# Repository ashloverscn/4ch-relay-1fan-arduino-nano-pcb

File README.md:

# 4ch-relay-1fan-arduino-nano-pcb
4ch-relay-1fan-arduino-nano-pcb

firmware written in arduino : 

https://github.com/ashloverscn/ArduinoNano-4ch_Relay_and_1_Fan

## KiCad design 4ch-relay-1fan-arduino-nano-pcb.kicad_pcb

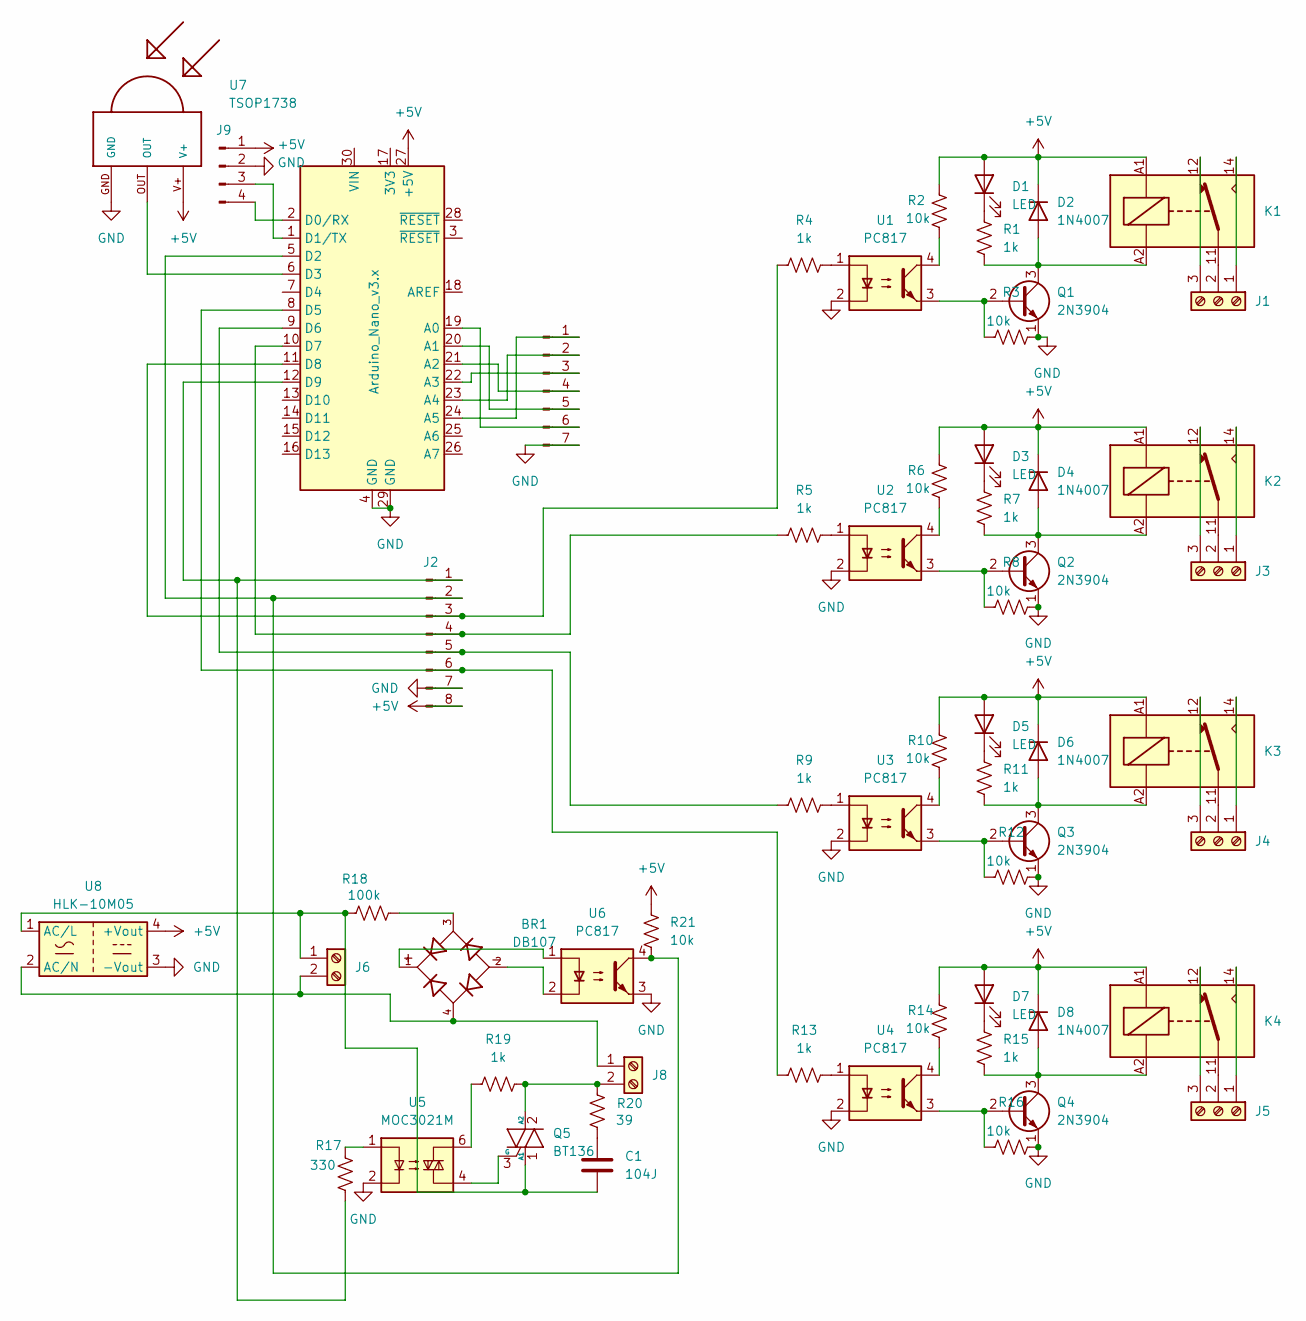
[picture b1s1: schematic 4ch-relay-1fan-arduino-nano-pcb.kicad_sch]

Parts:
A1: Arduino_Nano_v3.x; Arduino_Nano
BR1: DB107; DIP825W50P509L880H320Q4; PARTREV 13
C1: 104J; C_Disc_D16.0mm_W5.0mm_P10.00mm
D1, D3, D5, D7: LED; LED_D5.0mm
D2, D4, D6, D8: 1N4007; D_DO-41_SOD81_P10.16mm_Horizontal
J1, J3, J4, J5: Screw_Terminal_01x03; TerminalBlock_Phoenix_MKDS-1,5-3-5.08_1x03_P5.08mm_Horizont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
J2: Conn_01x08_Pin; PinHeader_1x08_P2.54mm_Vertical
J6, J8: TerminalBlock_MaiXu_MX126-5.0-02P_1x02_P5.00mm
J7: Conn_01x07_Pin; PinHeader_1x07_P2.54mm_Vertical
J9: Conn_01x04_Pin; PinHeader_1x04_P2.54mm_Vertical
K1, K2, K3, K4: Relay_SPDT; Relay_SPDT_Finder_36.11
Q1, Q2, Q3, Q4: 2N3904; TO-92_Inline
Q5: BT136; TO-220-3_Vertical
R1, R4, R5, R7, R9, R11, R13, R15: 1k; R_Axial_DIN0207_L6.3mm_D2.5mm_P10.16mm_Horizontal
R2, R3, R6, R8, R10, R12, R14, R16: 10k; R_Axial_DIN0207_L6.3mm_D2.5mm_P10.16mm_Horizontal
R17: 330; R_Axial_DIN0207_L6.3mm_D2.5mm_P2.54mm_Vertical
R18: 100k; R_Axial_DIN0207_L6.3mm_D2.5mm_P5.08mm_Vertical
R19: 1k; R_Axial_DIN0207_L6.3mm_D2.5mm_P2.54mm_Vertical
R20: 39; R_Axial_DIN0207_L6.3mm_D2.5mm_P5.08mm_Vertical
R21: 10k; R_Axial_DIN0207_L6.3mm_D2.5mm_P2.54mm_Vertical
U1, U2, U3, U4: PC817; DIP-4_W7.62mm
U5: MOC3021M; DIP-6_W7.62mm_LongPads
U6: PC817; DIP-4_W7.62mm_LongPads
U7: TSOP1738; TSOP17XX
U8: HLK-10M05; Converter_ACDC_Hi-Link_HLK-10Mxx

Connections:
+5V: A1.27 (+5V), D1.2 (A), D2.1 (K), D3.2 (A), D4.1 (K), D5.2 (A), D6.1 (K), D7.2 (A), D8.1 (K), J2.8, J9.1, K1.A1, K2.A1, K3.A1, K4.A1, R2.2, R6.2, R10.2, R14.2, R21.1, U7.V+, U8.4 (+Vout)
GND: A1.4 (GND), A1.29 (GND), J2.7, J7.7, J9.2, Q1.1 (E), Q2.1 (E), Q3.1 (E), Q4.1 (E), R3.1, R8.1, R12.1, R16.1, U1.2, U2.2, U3.2, U4.2, U5.2, U6.3, U7.GND, U8.3 (-Vout)
unnamed: A1.19 (A0), J7.6
unnamed: A1.20 (A1), J7.5
unnamed: A1.21 (A2), J7.4
unnamed: A1.22 (A3), J7.3
unnamed: A1.23 (A4), J7.2
unnamed: A1.24 (A5), J7.1
unnamed: A1.2 (D0/RX), J9.4
unnamed: A1.1 (D1/TX), J9.3
unnamed: A1.5 (D2), J2.2, R21.2, U6.4
unnamed: A1.6 (D3), U7.OUT
unnamed: A1.8 (D5), J2.6, R13.1
unnamed: A1.9 (D6), J2.5, R9.1
unnamed: A1.10 (D7), J2.4, R5.1
unnamed: A1.11 (D8), J2.3, R4.1
unnamed: A1.12 (D9), J2.1, R17.2
unnamed: BR1.1, U6.1
unnamed: BR1.2, U6.2
unnamed: BR1.3, R18.2
unnamed: C1.1, R20.2
unnamed: D1.1 (K), R1.1
unnamed: D2.2 (A), K1.A2, Q1.3 (C), R1.2
unnamed: D3.1 (K), R7.1
unnamed: D4.2 (A), K2.A2, Q2.3 (C), R7.2
unnamed: D5.1 (K), R11.1
unnamed: D6.2 (A), K3.A2, Q3.3 (C), R11.2
unnamed: D7.1 (K), R15.1
unnamed: D8.2 (A), K4.A2, Q4.3 (C), R15.2
unnamed: J1.1, K1.14
unnamed: J1.2, K1.11
unnamed: J1.3, K1.12
unnamed: J3.1, K2.14
unnamed: J3.2, K2.11
unnamed: J3.3, K2.12
unnamed: J4.1, K3.14
unnamed: J4.2, K3.11
unnamed: J4.3, K3.12
unnamed: J5.1, K4.14
unnamed: J5.2, K4.11
unnamed: J5.3, K4.12
unnamed: C1.2, J6.1, Q5.1 (A1), R18.1, U8.1 (AC/L)
unnamed: BR1.4, J6.2, J8.1, U8.2 (AC/N)
unnamed: J8.2, Q5.2 (A2), R19.1, R20.1
unnamed: Q1.2 (B), R3.2, U1.3
unnamed: Q2.2 (B), R8.2, U2.3
unnamed: Q3.2 (B), R12.2, U3.3
unnamed: Q4.2 (B), R16.2, U4.3
unnamed: Q5.3 (G), U5.4
unnamed: R2.1, U1.4
unnamed: R4.2, U1.1
unnamed: R5.2, U2.1
unnamed: R6.1, U2.4
unnamed: R9.2, U3.1
unnamed: R10.1, U3.4
unnamed: R13.2, U4.1
unnamed: R14.1, U4.4
unnamed: R17.1, U5.1
unnamed: R19.2, U5.6

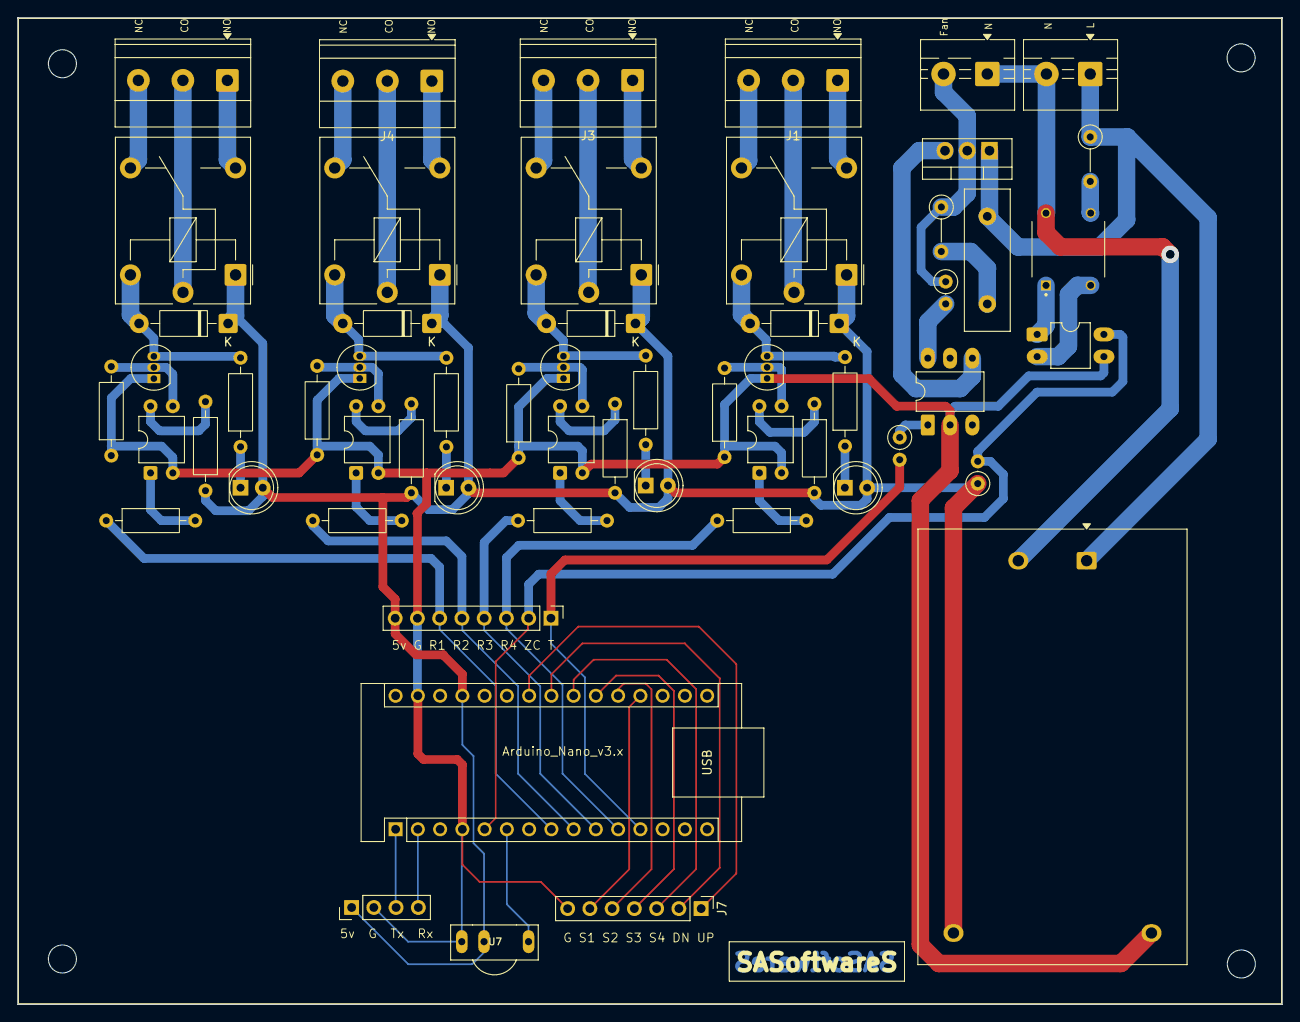
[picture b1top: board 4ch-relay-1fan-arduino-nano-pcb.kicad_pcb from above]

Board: 2 copper layers, 144.3 x 112.6 mm, 58 parts (0 on the bottom side), 59 nets.
